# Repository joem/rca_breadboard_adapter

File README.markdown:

RCA Breadboard Adapter
======================

This is a breadboard adapter for accommodating two vertical RCA connectors, specifically ones from CUI Devices RCJ-02 series. (I specifically like RCJ-024 since its yellow and I intend to use these for video.) It’s based on [a similar board I made for Thonkiconn-style 3.5mm mono jacks](https://oshpark.com/shared_projects/N9XmX8cB). This one uses a ground plane and thicker traces, just in case it matters for my video use cases. The middle (unlabeled) pins for each connector do nothing.

> :information_source: _Note: The grounds are not connected to each other on the board. I did it this way so that you can pass two wildly different signals through the jacks independently if desired. (In truth, there probably aren't very many use cases where this is necessary.)_

This was designed as a KiCad project, but if you want to fabricate a PCB you don't need KiCad since the gerbers are in the [gerbers folder](gerbers/). Also, there's a PDF schematic in the [pdfs directory](pdfs) though it's incredibly simple. And if you just want to order PCBs, [there's an OSHPark project](https://oshpark.com/shared_projects/sYbP0NE6).

Opening the KiCad project requires KiCad 6 at a minimum. I've removed the old KiCad 5 files.

## BOM:

- (2) CUI Devices RCJ-024 Yellow RCA Phono Connectors (or a different color from the RCJ-02 series) [Mouser part #: 490-RCJ-024]
- (2) 2x3 0.1"-spacing pin headers

## Render from KiCad:

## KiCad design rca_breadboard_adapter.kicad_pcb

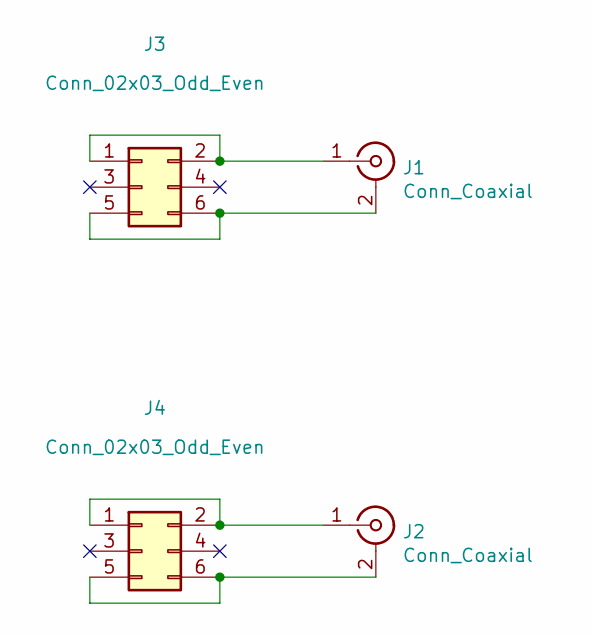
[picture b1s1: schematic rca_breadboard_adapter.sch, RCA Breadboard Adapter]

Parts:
J1, J2: Conn_Coaxial; RCA-Phono_CUI-Devices_RCJ-02X_Vertical
J3, J4: Conn_02x03_Odd_Even; PinHeader_2x03_P2.54mm_Vertical

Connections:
unnamed: J1.1 (In), J3.1, J3.2
unnamed: J1.2 (Ext), J3.5, J3.6
unnamed: J2.1 (In), J4.1, J4.2
unnamed: J2.2 (Ext), J4.5, J4.6

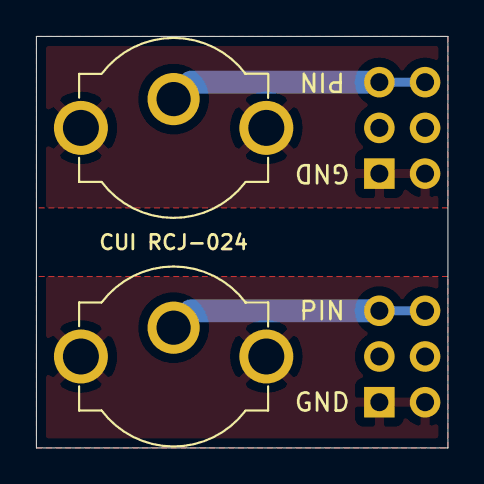
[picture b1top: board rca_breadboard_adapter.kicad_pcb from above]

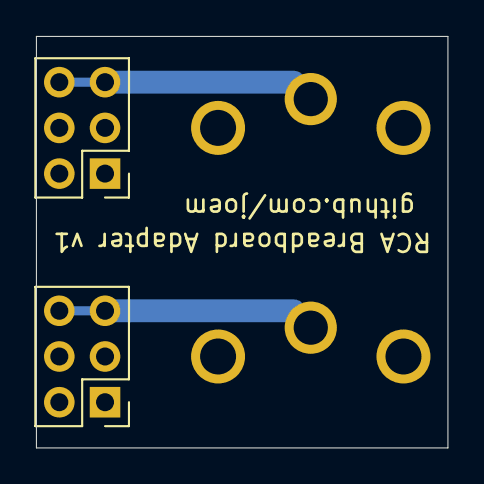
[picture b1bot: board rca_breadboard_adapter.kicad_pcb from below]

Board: 2 copper layers, 22.9 x 22.9 mm, 4 parts (2 on the bottom side), 4 nets.

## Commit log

2020-04-09 Add gerbers, images, and pdfs
2020-04-09 Add readme
2020-04-09 Update readme about separate grounds
2020-04-22 Update silkscreen with github URL
2023-04-02 Update project to kicad 6+
2023-04-02 Add .gitignore
